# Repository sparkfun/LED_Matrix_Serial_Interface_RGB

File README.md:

LED Matrix Serial Interface-RGB
===============================

[  
*LED Matrix - Serial Interface RGB (COM-00760)*](https://www.sparkfun.com/products/760)

This is a large sized RGB LED matrix with a backpack that has been designed to take SPI serial input and display any graphics you pass it.

Repository Contents
-------------------
* **/Firmware** - Any firmware that the part ships with, 
* **/Hardware** - All Eagle design files (.brd, .sch, .STL)

License Information
-------------------
The hardware is released under [Creative Commons Share-alike 3.0](http://creativecommons.org/licenses/by-sa/3.0/).  
All other code is open source so please feel free to do anything you want with it; you buy me a beer if you use this and we meet someday ([Beerware license](http://en.wikipedia.org/wiki/Beerware)).

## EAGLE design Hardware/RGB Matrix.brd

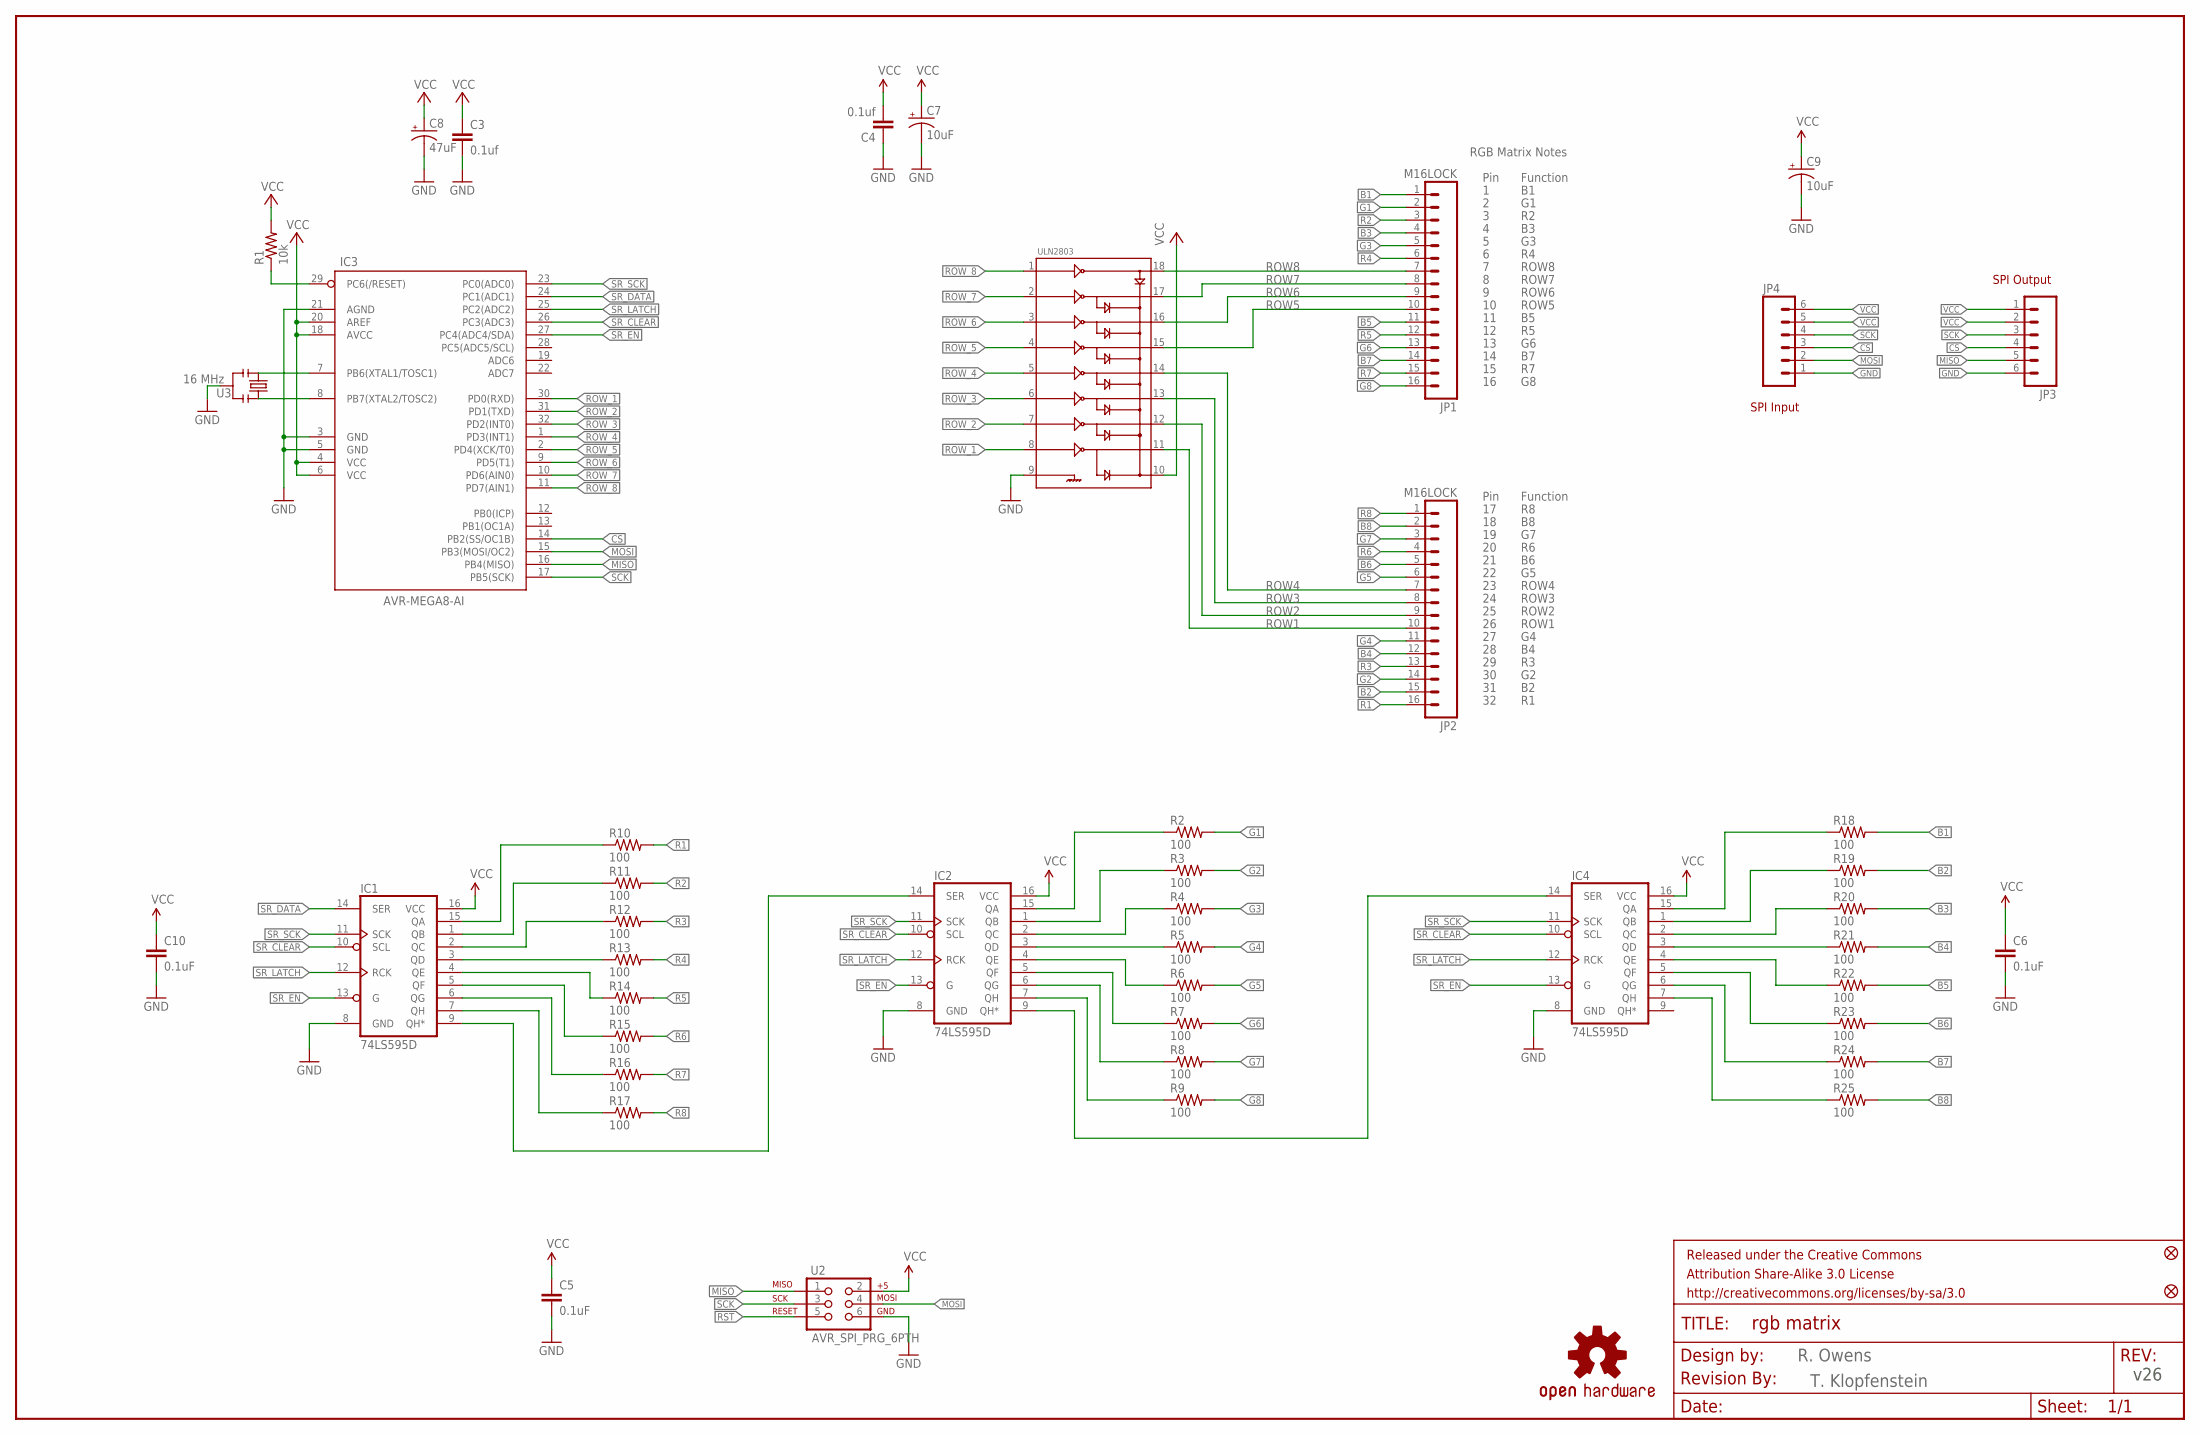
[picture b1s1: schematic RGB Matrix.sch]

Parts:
C3, C4: 0.1uf; 0603-CAP
C5, C6, C10: 0.1uF; 0603-CAP
C7, C9: 10uF; EIA3216
C8: 47uF; EIA3528
FRAME1: FRAME-LEDGER; CREATIVE_COMMONS
IC1, IC2, IC4: 74LS595D; SO16
IC3: AVR-MEGA8-AI; TQFP32-08
JP1, JP2: M16LOCK; 1X16_LOCK
JP3: M06SMD; 1X06-SMD
JP4: M06LOCK; 1X06_LOCK
LOGO1: OSHW-LOGOL; OSHW-LOGO-L
R1: 10k; 0603-RES
R2, R3, R4, R5, R6, R7, R8, R9, R10, R11, R12, R13, R14, R15, R16, R17, R18, R19, R20, R21, R22, R23, R24, R25: 100; 0603-RES
U2: AVR_SPI_PRG_6PTH; 2X3
U3: 16 MHz; RESONATOR-SMD
U$1, U$3: FIDUCIAL1X2; FIDUCIAL-1X2
U$2: REVISION
ULN2803: ULN2803SOICW; SO18L

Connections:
B1: JP1.1, R18.2
B2: JP2.15, R19.2
B3: JP1.4, R20.2
B4: JP2.12, R21.2
B5: JP1.11, R22.2
B6: JP2.5, R23.2
B7: JP1.14, R24.2
B8: JP2.2, R25.2
CS: IC3.14 (PB2(SS/OC1B)), JP3.4, JP4.3
G1: JP1.2, R2.2
G2: JP2.14, R3.2
G3: JP1.5, R4.2
G4: JP2.11, R5.2
G5: JP2.6, R6.2
G6: JP1.13, R7.2
G7: JP2.3, R8.2
G8: JP1.16, R9.2
GND: C3.2, C4.1, C5.2, C6.2, C7.C (-), C8.C (-), C9.C (-), C10.2, IC1.8 (GND), IC2.8 (GND), IC3.3 (GND), IC3.5 (GND), IC3.21 (AGND), IC4.8 (GND), JP3.6, JP4.1, U2.6, U3.2, ULN2803.9
MISO: IC3.16 (PB4(MISO)), JP3.5, U2.1
MOSI: IC3.15 (PB3(MOSI/OC2)), JP4.2, U2.4
unnamed: IC3.7 (PB6(XTAL1/TOSC1)), U3.1
unnamed: IC3.8 (PB7(XTAL2/TOSC2)), U3.3
unnamed: IC1.9 (QH*), IC2.14 (SER)
unnamed: IC1.15 (QA), R10.1
unnamed: IC1.1 (QB), R11.1
unnamed: IC1.2 (QC), R12.1
unnamed: IC1.3 (QD), R13.1
unnamed: IC2.9 (QH*), IC4.14 (SER)
unnamed: IC1.4 (QE), R14.1
unnamed: IC1.5 (QF), R15.1
unnamed: IC1.6 (QG), R16.1
unnamed: IC1.7 (QH), R17.1
unnamed: IC2.15 (QA), R2.1
unnamed: IC2.1 (QB), R3.1
unnamed: IC2.2 (QC), R4.1
unnamed: IC2.3 (QD), R5.1
unnamed: IC2.4 (QE), R6.1
unnamed: IC2.5 (QF), R7.1
unnamed: IC2.6 (QG), R8.1
unnamed: IC2.7 (QH), R9.1
unnamed: IC4.15 (QA), R18.1
unnamed: IC4.1 (QB), R19.1
unnamed: IC4.2 (QC), R20.1
unnamed: IC4.3 (QD), R21.1
unnamed: IC4.4 (QE), R22.1
unnamed: IC4.5 (QF), R23.1
unnamed: IC4.6 (QG), R24.1
unnamed: IC4.7 (QH), R25.1
R1: JP2.16, R10.2
R2: JP1.3, R11.2
R3: JP2.13, R12.2
R4: JP1.6, R13.2
R5: JP1.12, R14.2
R6: JP2.4, R15.2
R7: JP1.15, R16.2
R8: JP2.1, R17.2
ROW1: JP2.10, ULN2803.11
ROW2: JP2.9, ULN2803.12
ROW3: JP2.8, ULN2803.13
ROW4: JP2.7, ULN2803.14
ROW5: JP1.10, ULN2803.15
ROW6: JP1.9, ULN2803.16
ROW7: JP1.8, ULN2803.17
ROW8: JP1.7, ULN2803.18
ROW_1: IC3.30 (PD0(RXD)), ULN2803.8
ROW_2: IC3.31 (PD1(TXD)), ULN2803.7
ROW_3: IC3.32 (PD2(INT0)), ULN2803.6
ROW_4: IC3.1 (PD3(INT1)), ULN2803.5
ROW_5: IC3.2 (PD4(XCK/T0)), ULN2803.4
ROW_6: IC3.9 (PD5(T1)), ULN2803.3
ROW_7: IC3.10 (PD6(AIN0)), ULN2803.2
ROW_8: IC3.11 (PD7(AIN1)), ULN2803.1
RST: IC3.29 (PC6(/RESET)), R1.1, U2.5
SCK: IC3.17 (PB5(SCK)), JP3.3, JP4.4, U2.3
SR_CLEAR: IC1.10 (SCL), IC2.10 (SCL), IC3.26 (PC3(ADC3)), IC4.10 (SCL)
SR_DATA: IC1.14 (SER), IC3.24 (PC1(ADC1))
SR_EN: IC1.13 (G), IC2.13 (G), IC3.27 (PC4(ADC4/SDA)), IC4.13 (G)
SR_LATCH: IC1.12 (RCK), IC2.12 (RCK), IC3.25 (PC2(ADC2)), IC4.12 (RCK)
SR_SCK: IC1.11 (SCK), IC2.11 (SCK), IC3.23 (PC0(ADC0)), IC4.11 (SCK)
VCC: C3.1, C4.2, C5.1, C6.1, C7.A (+), C8.A (+), C9.A (+), C10.1, IC1.16 (VCC), IC2.16 (VCC), IC3.4 (VCC), IC3.6 (VCC), IC3.18 (AVCC), IC3.20 (AREF), IC4.16 (VCC), JP3.1, JP3.2, JP4.5, JP4.6, R1.2, U2.2, ULN2803.10

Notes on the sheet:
Pin
Function
ROW8
ROW7
ROW6
ROW5
ROW4
ROW3
RGB Matrix Notes
ROW2
ROW1
SPI Output
SPI Input
R. Owens
v26
T. Klopfenstein

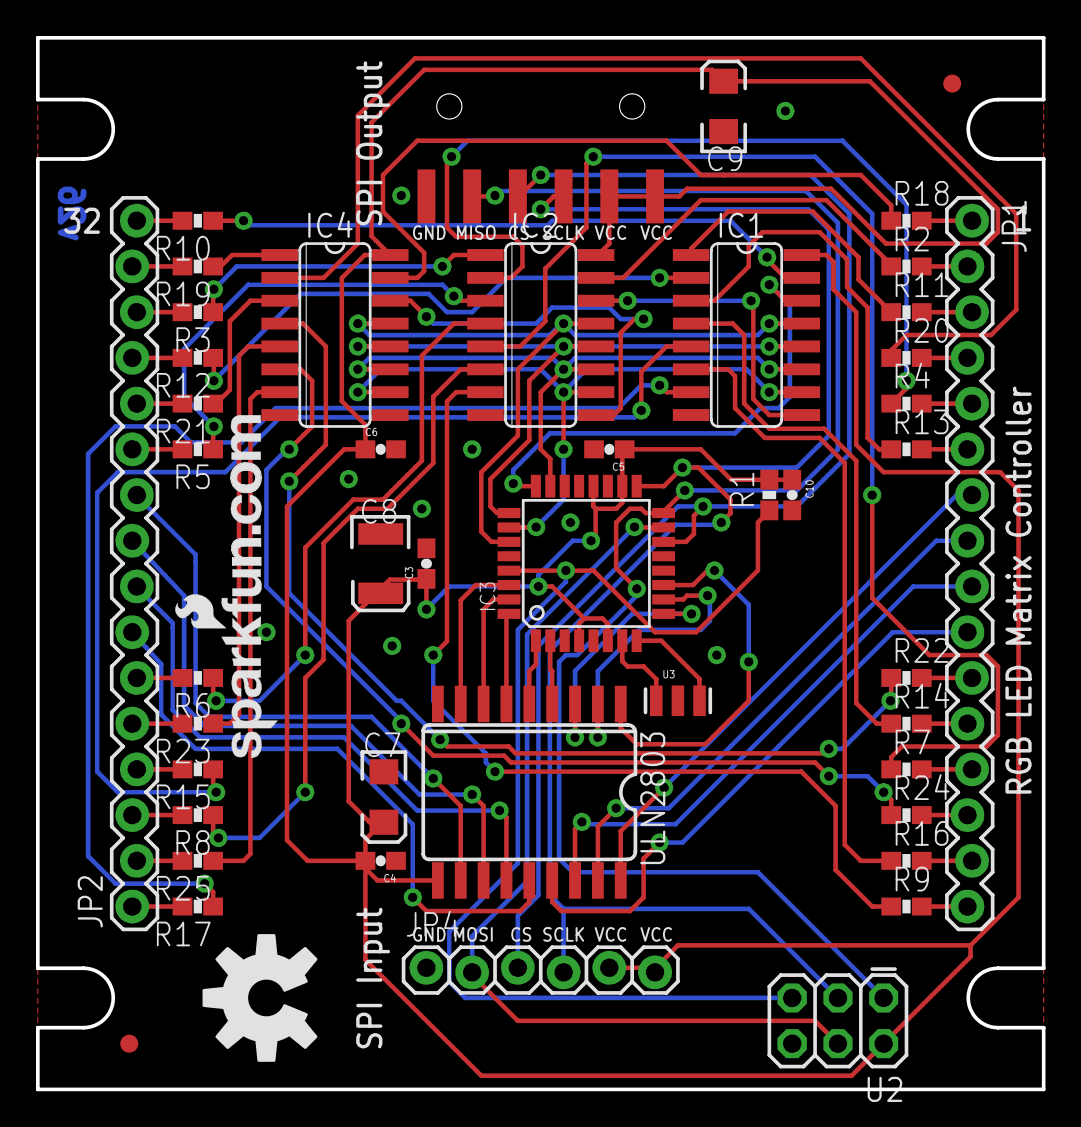
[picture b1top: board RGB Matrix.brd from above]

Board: 2 copper layers, 55.9 x 58.4 mm, 50 parts (0 on the bottom side), 80 nets.

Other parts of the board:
U$8: SFE-NEW-WEBLOGO

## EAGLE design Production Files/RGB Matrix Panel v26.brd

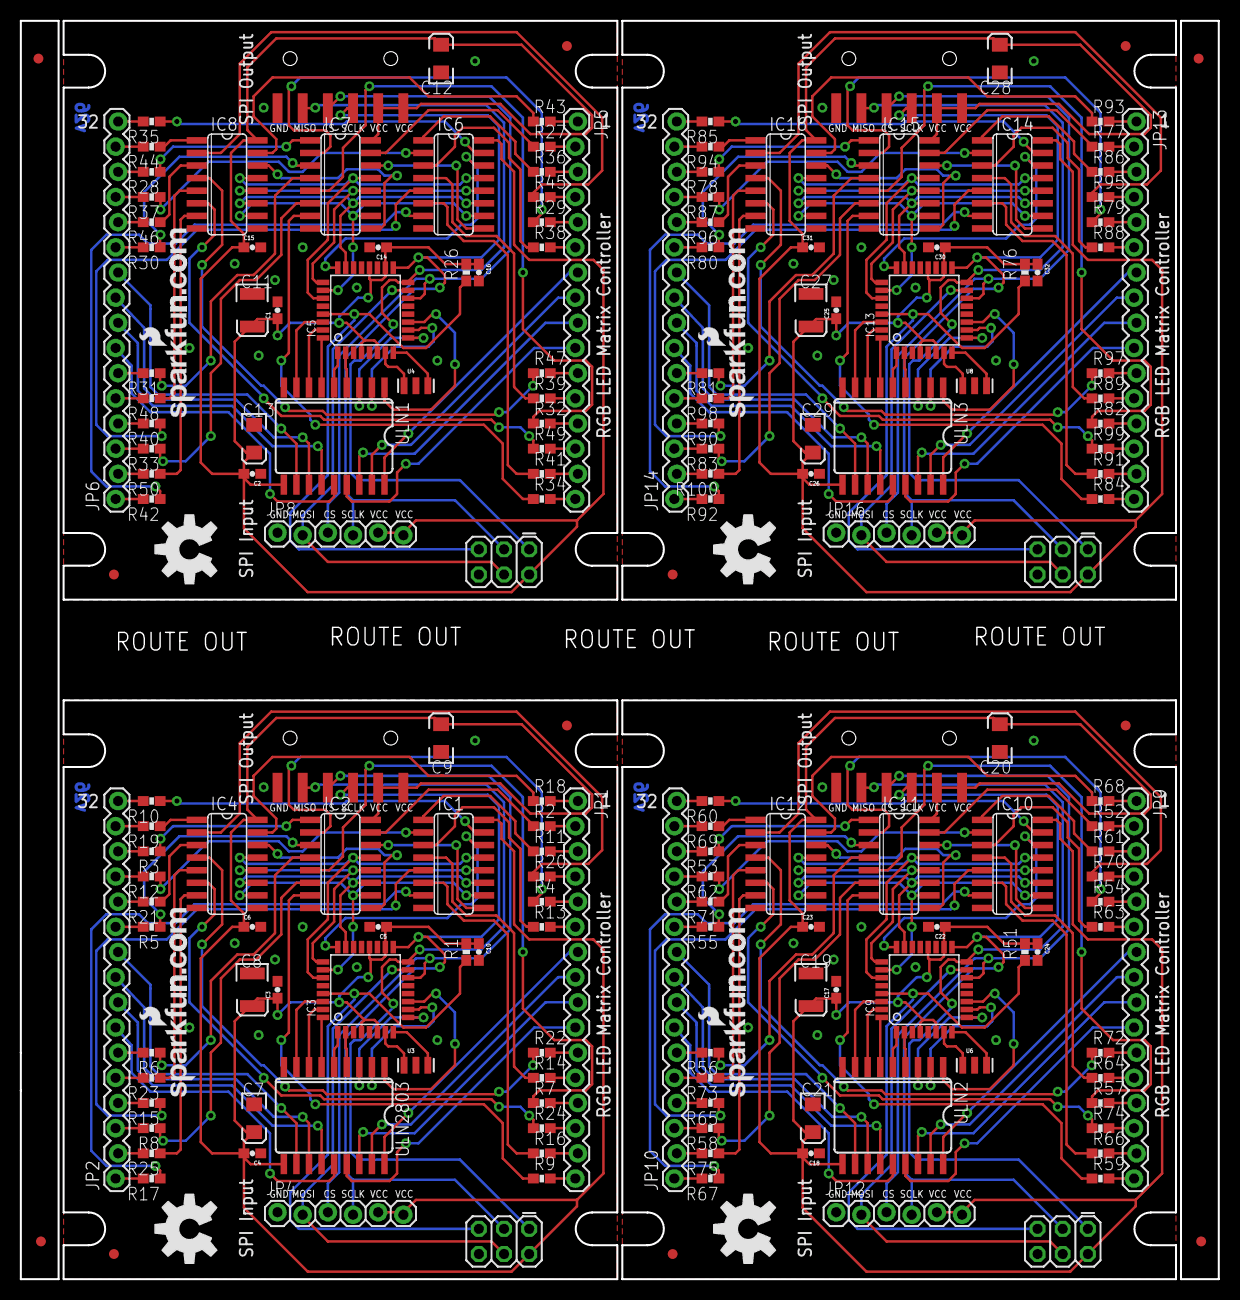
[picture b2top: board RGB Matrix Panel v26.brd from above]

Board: 2 copper layers, 120.9 x 127.0 mm, 196 parts (0 on the bottom side), 320 nets.

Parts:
C1, C2, C3, C4, C17, C18, C25, C26: 0.1uf; 0603-CAP
C5, C6, C10, C14, C15, C16, C22, C23, C24, C30, C31, C32: 0.1uF; 0603-CAP
C7, C9, C12, C13, C20, C21, C28, C29: 10uF; EIA3216
C8, C11, C19, C27: 47uF; EIA3528
E$1, E$2, E$3, E$4: FIDUCIAL-1X2
IC1, IC2, IC4, IC6, IC7, IC8, IC10, IC11, IC12, IC14, IC15, IC16: 74LS595D; SO16
IC3, IC5, IC9, IC13: AVR-MEGA8-AI; TQFP32-08
JP1, JP2, JP5, JP6, JP9, JP10, JP13, JP14: M16LOCK; 1X16_LOCK
JP3, JP7, JP11, JP15: 1X06-SMD
JP4, JP8, JP12, JP16: 1X06_LOCK
LOGO1, LOGO2, LOGO3, LOGO4: OSHW-LOGOL; OSHW-LOGO-L
R1, R26, R51, R76: 10k; 0603-RES
R2, R3, R4, R5, R6, R7, R8, R9, R10, R11, R12, R13, R14, R15, R16, R17, R18, R19, R20, R21, R22, R23, R24, R25, R27, R28, R29, R30, R31, R32, R33, R34, R35, R36, R37, R38, R39, R40, R41, R42, R43, R44, R45, R46, R47, R48, R49, R50, R52, R53, R54, R55, R56, R57, R58, R59, R60, R61, R62, R63, R64, R65, R66, R67, R68, R69, R70, R71, R72, R73, R74, R75, R77, R78, R79, R80, R81, R82, R83, R84, R85, R86, R87, R88, R89, R90, R91, R92, R93, R94, R95, R96, R97, R98, R99, R100: 100; 0603-RES
U1, U2, U5, U7: AVR_SPI_PRG_6PTH; 2X3
U3, U4, U6, U8: 16 MHz; RESONATOR-SMD
U$1, U$2, U$3, U$4, U$6, U$7, U$10, U$11: FIDUCIAL1X2; FIDUCIAL-1X2
U$5, U$8, U$9, U$12: SFE-NEW-WEBLOGO
ULN1, ULN2, ULN3, ULN2803: SO18L

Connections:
B1: JP1.1, R18.2
B2: JP2.15, R19.2
B3: JP1.4, R20.2
B4: JP2.12, R21.2
B5: JP1.11, R22.2
B6: JP2.5, R23.2
B7: JP1.14, R24.2
B8: JP2.2, R25.2
B9: JP5.1, R43.2
B10: JP6.15, R44.2
B11: JP5.4, R45.2
B12: JP6.12, R46.2
B13: JP5.11, R47.2
B14: JP6.5, R48.2
B15: JP5.14, R49.2
B16: JP6.2, R50.2
B17: JP9.1, R68.2
B18: JP10.15, R69.2
B19: JP9.4, R70.2
B20: JP10.12, R71.2
B21: JP9.11, R72.2
B22: JP10.5, R73.2
B23: JP9.14, R74.2
B24: JP10.2, R75.2
B25: JP13.1, R93.2
B26: JP14.15, R94.2
B27: JP13.4, R95.2
B28: JP14.12, R96.2
B29: JP13.11, R97.2
B30: JP14.5, R98.2
B31: JP13.14, R99.2
B32: JP14.2, R100.2
CS: IC3.14, JP3.4, JP4.3
CS1: IC5.14, JP7.4, JP8.3
CS2: IC9.14, JP11.4, JP12.3
CS3: IC13.14, JP15.4, JP16.3
G1: JP1.2, R2.2
G2: JP2.14, R3.2
G3: JP1.5, R4.2
G4: JP2.11, R5.2
G5: JP2.6, R6.2
G6: JP1.13, R7.2
G7: JP2.3, R8.2
G8: JP1.16, R9.2
G9: JP5.2, R27.2
G10: JP6.14, R28.2
G11: JP5.5, R29.2
G12: JP6.11, R30.2
G13: JP6.6, R31.2
G14: JP5.13, R32.2
G15: JP6.3, R33.2
G16: JP5.16, R34.2
G17: JP9.2, R52.2
G18: JP10.14, R53.2
G19: JP9.5, R54.2
G20: JP10.11, R55.2
G21: JP10.6, R56.2
G22: JP9.13, R57.2
G23: JP10.3, R58.2
G24: JP9.16, R59.2
G25: JP13.2, R77.2
G26: JP14.14, R78.2
G27: JP13.5, R79.2
G28: JP14.11, R80.2
G29: JP14.6, R81.2
G30: JP13.13, R82.2
G31: JP14.3, R83.2
G32: JP13.16, R84.2
GND: C3.2, C4.1, C5.2, C6.2, C7.C, C8.C, C9.C, C10.2, IC1.8, IC2.8, IC3.3, IC3.5, IC3.21, IC4.8, JP3.6, JP4.1, U2.6, U3.2, ULN2803.9
GND1: C1.2, C2.1, C11.C, C12.C, C13.C, C14.2, C15.2, C16.2, IC5.3, IC5.5, IC5.21, IC6.8, IC7.8, IC8.8, JP7.6, JP8.1, U1.6, U4.2, ULN1.9
GND2: C17.2, C18.1, C19.C, C20.C, C21.C, C22.2, C23.2, C24.2, IC9.3, IC9.5, IC9.21, IC10.8, IC11.8, IC12.8, JP11.6, JP12.1, U5.6, U6.2, ULN2.9
GND3: C25.2, C26.1, C27.C, C28.C, C29.C, C30.2, C31.2, C32.2, IC13.3, IC13.5, IC13.21, IC14.8, IC15.8, IC16.8, JP15.6, JP16.1, U7.6, U8.2, ULN3.9
MISO: IC3.16, JP3.5, U2.1
MISO1: IC5.16, JP7.5, U1.1
MISO2: IC9.16, JP11.5, U5.1
MISO3: IC13.16, JP15.5, U7.1
MOSI: IC3.15, JP4.2, U2.4
MOSI1: IC5.15, JP8.2, U1.4
MOSI2: IC9.15, JP12.2, U5.4
MOSI3: IC13.15, JP16.2, U7.4
unnamed: IC3.7, U3.1
unnamed: IC3.8, U3.3
unnamed: IC6.15, R35.1
unnamed: IC6.1, R36.1
unnamed: IC6.2, R37.1
unnamed: IC6.3, R38.1
unnamed: IC6.4, R39.1
unnamed: IC6.5, R40.1
unnamed: IC6.6, R41.1
unnamed: IC6.7, R42.1
unnamed: IC1.9, IC2.14
unnamed: IC1.15, R10.1
unnamed: IC1.1, R11.1
unnamed: IC1.2, R12.1
unnamed: IC1.3, R13.1
unnamed: IC2.9, IC4.14
unnamed: IC7.15, R27.1
unnamed: IC1.4, R14.1
unnamed: IC1.5, R15.1
unnamed: IC1.6, R16.1
unnamed: IC1.7, R17.1
unnamed: IC2.15, R2.1
unnamed: IC2.1, R3.1
unnamed: IC2.2, R4.1
unnamed: IC2.3, R5.1
unnamed: IC2.4, R6.1
unnamed: IC2.5, R7.1
unnamed: IC2.6, R8.1
unnamed: IC2.7, R9.1
unnamed: IC7.1, R28.1
unnamed: IC7.2, R29.1
unnamed: IC4.15, R18.1
unnamed: IC4.1, R19.1
unnamed: IC4.2, R20.1
unnamed: IC4.3, R21.1
unnamed: IC4.4, R22.1
unnamed: IC4.5, R23.1
unnamed: IC4.6, R24.1
unnamed: IC4.7, R25.1
unnamed: IC7.3, R30.1
unnamed: IC7.4, R31.1
unnamed: IC7.5, R32.1
unnamed: IC7.6, R33.1
unnamed: IC7.7, R34.1
unnamed: IC8.15, R43.1
unnamed: IC8.1, R44.1
unnamed: IC8.2, R45.1
unnamed: IC8.3, R46.1
unnamed: IC8.4, R47.1
unnamed: IC8.5, R48.1
unnamed: IC8.6, R49.1
unnamed: IC8.7, R50.1
unnamed: IC6.9, IC7.14
unnamed: IC7.9, IC8.14
unnamed: IC5.7, U4.1
unnamed: IC5.8, U4.3
unnamed: IC10.15, R60.1
unnamed: IC10.1, R61.1
unnamed: IC10.2, R62.1
unnamed: IC10.3, R63.1
unnamed: IC10.4, R64.1
unnamed: IC10.5, R65.1
unnamed: IC10.6, R66.1
unnamed: IC10.7, R67.1
unnamed: IC11.15, R52.1
unnamed: IC11.1, R53.1
unnamed: IC11.2, R54.1
unnamed: IC11.3, R55.1
unnamed: IC11.4, R56.1
unnamed: IC11.5, R57.1
unnamed: IC11.6, R58.1
unnamed: IC11.7, R59.1
unnamed: IC12.15, R68.1
unnamed: IC12.1, R69.1
unnamed: IC12.2, R70.1
unnamed: IC12.3, R71.1
unnamed: IC12.4, R72.1
unnamed: IC12.5, R73.1
unnamed: IC12.6, R74.1
unnamed: IC12.7, R75.1
unnamed: IC10.9, IC11.14
unnamed: IC11.9, IC12.14
unnamed: IC9.7, U6.1
unnamed: IC9.8, U6.3
unnamed: IC14.15, R85.1
unnamed: IC14.1, R86.1
unnamed: IC14.2, R87.1
unnamed: IC14.3, R88.1
unnamed: IC14.4, R89.1
unnamed: IC14.5, R90.1
unnamed: IC14.6, R91.1
unnamed: IC14.7, R92.1
unnamed: IC15.15, R77.1
unnamed: IC15.1, R78.1
unnamed: IC15.2, R79.1
unnamed: IC15.3, R80.1
unnamed: IC15.4, R81.1
unnamed: IC15.5, R82.1
unnamed: IC15.6, R83.1
unnamed: IC15.7, R84.1
unnamed: IC16.15, R93.1
unnamed: IC16.1, R94.1
unnamed: IC16.2, R95.1
unnamed: IC16.3, R96.1
unnamed: IC16.4, R97.1
unnamed: IC16.5, R98.1
unnamed: IC16.6, R99.1
unnamed: IC16.7, R100.1
unnamed: IC14.9, IC15.14
unnamed: IC15.9, IC16.14
unnamed: IC13.7, U8.1
unnamed: IC13.8, U8.3
R1: JP2.16, R10.2
R2: JP1.3, R11.2
R3: JP2.13, R12.2
R4: JP1.6, R13.2
R5: JP1.12, R14.2
R6: JP2.4, R15.2
R7: JP1.15, R16.2
R8: JP2.1, R17.2
R9: JP6.16, R35.2
R10: JP5.3, R36.2
R11: JP6.13, R37.2
R12: JP5.6, R38.2
R13: JP5.12, R39.2
R14: JP6.4, R40.2
R15: JP5.15, R41.2
R16: JP6.1, R42.2
R17: JP10.16, R60.2
R18: JP9.3, R61.2
R19: JP10.13, R62.2
R20: JP9.6, R63.2
R21: JP9.12, R64.2
R22: JP10.4, R65.2
R23: JP9.15, R66.2
R24: JP10.1, R67.2
R25: JP14.16, R85.2
R26: JP13.3, R86.2
R27: JP14.13, R87.2
R28: JP13.6, R88.2
R29: JP13.12, R89.2
R30: JP14.4, R90.2
R31: JP13.15, R91.2
R32: JP14.1, R92.2
ROW1: JP2.10, ULN2803.11
ROW2: JP2.9, ULN2803.12
ROW3: JP2.8, ULN2803.13
ROW4: JP2.7, ULN2803.14
ROW5: JP1.10, ULN2803.15
ROW6: JP1.9, ULN2803.16
ROW7: JP1.8, ULN2803.17
ROW8: JP1.7, ULN2803.18
ROW9: JP5.7, ULN1.18
ROW10: JP5.8, ULN1.17
ROW11: JP5.9, ULN1.16
ROW12: JP5.10, ULN1.15
ROW13: JP6.7, ULN1.14
ROW14: JP6.8, ULN1.13
ROW15: JP6.9, ULN1.12
ROW16: JP6.10, ULN1.11
ROW17: JP9.7, ULN2.18
ROW18: JP9.8, ULN2.17
ROW19: JP9.9, ULN2.16
ROW20: JP9.10, ULN2.15
ROW21: JP10.7, ULN2.14
ROW22: JP10.8, ULN2.13
ROW23: JP10.9, ULN2.12
ROW24: JP10.10, ULN2.11
ROW25: JP13.7, ULN3.18
ROW26: JP13.8, ULN3.17
ROW27: JP13.9, ULN3.16
ROW28: JP13.10, ULN3.15
ROW29: JP14.7, ULN3.14
ROW30: JP14.8, ULN3.13
ROW31: JP14.9, ULN3.12
ROW32: JP14.10, ULN3.11
ROW_1: IC3.30, ULN2803.8
ROW_2: IC3.31, ULN2803.7
ROW_3: IC3.32, ULN2803.6
ROW_4: IC3.1, ULN2803.5
ROW_5: IC3.2, ULN2803.4
ROW_6: IC3.9, ULN2803.3
ROW_7: IC3.10, ULN2803.2
ROW_8: IC3.11, ULN2803.1
ROW_9: IC5.11, ULN1.1
ROW_10: IC5.10, ULN1.2
ROW_11: IC5.9, ULN1.3
ROW_12: IC5.2, ULN1.4
ROW_13: IC5.1, ULN1.5
ROW_14: IC5.32, ULN1.6
ROW_15: IC5.31, ULN1.7
ROW_16: IC5.30, ULN1.8
ROW_17: IC9.11, ULN2.1
ROW_18: IC9.10, ULN2.2
ROW_19: IC9.9, ULN2.3
ROW_20: IC9.2, ULN2.4
ROW_21: IC9.1, ULN2.5
ROW_22: IC9.32, ULN2.6
ROW_23: IC9.31, ULN2.7
ROW_24: IC9.30, ULN2.8
ROW_25: IC13.11, ULN3.1
ROW_26: IC13.10, ULN3.2
ROW_27: IC13.9, ULN3.3
ROW_28: IC13.2, ULN3.4
ROW_29: IC13.1, ULN3.5
ROW_30: IC13.32, ULN3.6
ROW_31: IC13.31, ULN3.7
ROW_32: IC13.30, ULN3.8
RST: IC3.29, R1.1, U2.5
RST1: IC5.29, R26.1, U1.5
RST2: IC9.29, R51.1, U5.5
RST3: IC13.29, R76.1, U7.5
SCK: IC3.17, JP3.3, JP4.4, U2.3
SCK1: IC5.17, JP7.3, JP8.4, U1.3
SCK2: IC9.17, JP11.3, JP12.4, U5.3
SCK3: IC13.17, JP15.3, JP16.4, U7.3
SR_CLEAR: IC1.10, IC2.10, IC3.26, IC4.10
SR_CLEAR1: IC5.26, IC6.10, IC7.10, IC8.10
SR_CLEAR2: IC9.26, IC10.10, IC11.10, IC12.10
SR_CLEAR3: IC13.26, IC14.10, IC15.10, IC16.10
SR_DATA: IC1.14, IC3.24
SR_DATA1: IC5.24, IC6.14
SR_DATA2: IC9.24, IC10.14
SR_DATA3: IC13.24, IC14.14
SR_EN: IC1.13, IC2.13, IC3.27, IC4.13
SR_EN1: IC5.27, IC6.13, IC7.13, IC8.13
SR_EN2: IC9.27, IC10.13, IC11.13, IC12.13
SR_EN3: IC13.27, IC14.13, IC15.13, IC16.13
SR_LATCH: IC1.12, IC2.12, IC3.25, IC4.12
SR_LATCH1: IC5.25, IC6.12, IC7.12, IC8.12
SR_LATCH2: IC9.25, IC10.12, IC11.12, IC12.12
SR_LATCH3: IC13.25, IC14.12, IC15.12, IC16.12
SR_SCK: IC1.11, IC2.11, IC3.23, IC4.11
SR_SCK1: IC5.23, IC6.11, IC7.11, IC8.11
SR_SCK2: IC9.23, IC10.11, IC11.11, IC12.11
SR_SCK3: IC13.23, IC14.11, IC15.11, IC16.11
VCC: C3.1, C4.2, C5.1, C6.1, C7.A, C8.A, C9.A, C10.1, IC1.16, IC2.16, IC3.4, IC3.6, IC3.18, IC3.20, IC4.16, JP3.1, JP3.2, JP4.5, JP4.6, R1.2, U2.2, ULN2803.10
VCC1: C1.1, C2.2, C11.A, C12.A, C13.A, C14.1, C15.1, C16.1, IC5.4, IC5.6, IC5.18, IC5.20, IC6.16, IC7.16, IC8.16, JP7.1, JP7.2, JP8.5, JP8.6, R26.2, U1.2, ULN1.10
VCC2: C17.1, C18.2, C19.A, C20.A, C21.A, C22.1, C23.1, C24.1, IC9.4, IC9.6, IC9.18, IC9.20, IC10.16, IC11.16, IC12.16, JP11.1, JP11.2, JP12.5, JP12.6, R51.2, U5.2, ULN2.10
VCC3: C25.1, C26.2, C27.A, C28.A, C29.A, C30.1, C31.1, C32.1, IC13.4, IC13.6, IC13.18, IC13.20, IC14.16, IC15.16, IC16.16, JP15.1, JP15.2, JP16.5, JP16.6, R76.2, U7.2, ULN3.10

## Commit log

2013-07-11 Updated board files for 0603 packages, OSHW logo
2013-07-11 Adding LED Matrix firmware and example code
2013-07-15 Updated revision to symbol
2013-07-17 Production ready v26
    created panel of 4
2014-10-24 Example Code Revision for Arduino
    -renaming sketch file (it's slightly confusing with the firmware that is on the serial backpack controller)
    -"ORANGE" actually is YELLOW when you mix red and green...
    -made the functions more modular so customers can call the functions from anywhere in the sketch file
    -added the set_matrix() function to set the position daisy chained matrix using the command char "0x25"
    -added some code to navigate through each daisy chained matrix to make sure that the array is cleared before writing to the matrices
    -added some lines to reset the frame index "0x26" using the command char before transferring so that Arduino can write to the LED matrix
2014-10-24 Remove old code
    Deleting old code with a revised Arduino sketch file that is more
    stable. The new firmware required some command lines to reset the frame
    index.
2014-10-27 Update Example_RGBMatrix.ino
    -Change character array to integer array for blank[]. This will cause problems in the future...
    -Modified matrix_write() to make the transfer more general for daisy chained LED Matrices.

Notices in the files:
parts and their libraries:
SparkFun-Aesthetics: Licensing: CC v3.0 Share-Alike You are welcome to use this library for commercial purposes.
SparkFun-Aesthetics: Released under the Creative Commons Attribution Share-Alike 3.0 License
SparkFun-Aesthetics: Released under the Creative Commons
